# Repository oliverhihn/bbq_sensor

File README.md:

# BBQ Temperature Sensor Project

This project is a BBQ temperature sensor that allows you to monitor the temperature of your BBQ grill or smoker remotely. It uses a Thermocouple with a MAX31855 amplifier temperature sensor to measure the temperature and an ESP8266 (D1 Mini) microcontroller to send the data to a web server. The project is designed to be easy to set up and use.

## PCB Setup

For a more stable and compact design, a custom PCB was created. The PCB is designed to hold the D1 Mini microcontroller and the MAX31855 amplifier.

image:

## ESPHome Setup

The project uses ESPHome to manage the D1 Mini microcontroller. ESPHome is a system that allows you to control your ESP8266/ESP32 devices through simple yet powerful configuration files and control them remotely through Home Assistant.

```yml
esp8266:
  board: d1_mini

spi:
  miso_pin: D0
  clk_pin: D1

sensor:
  - platform: max31855
    name: "BBQ Temperature"
    cs_pin: D2
    update_interval: 10s
```

## Parametric Box

Thank you to [@pbtec_14016](https://www.printables.com/@pbtec_14016) for the original design of the box. The original design was modified to fit the PCB and the D1 Mini microcontroller. The box is designed to be 3D printed and has cutouts for the thermocouple and the D1 Mini microcontroller.

Only things changed from the original design are the Holes in the wall of the box for the cables, the count of screws for the lid, and the dimensions.
The box is designed to be printed in one piece, with no need for supports. The design is parametric, allowing you to easily adjust the dimensions to fit your needs.

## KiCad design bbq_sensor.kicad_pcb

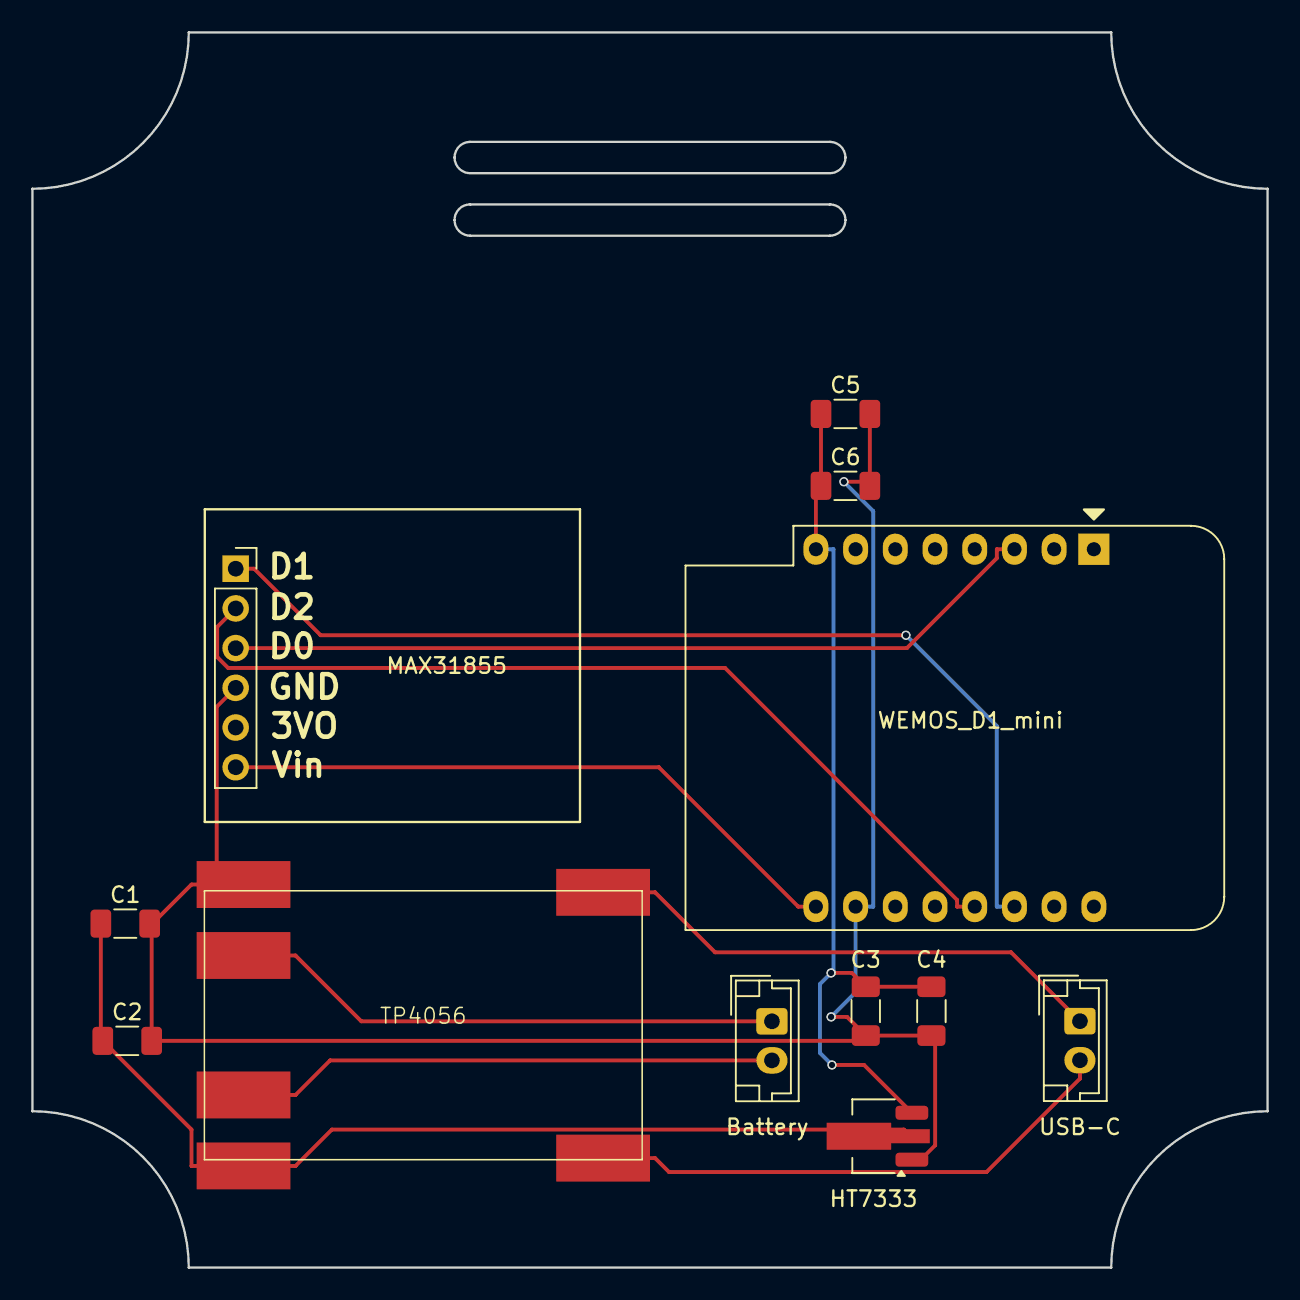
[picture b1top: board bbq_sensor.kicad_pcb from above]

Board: 2 copper layers, 79.0 x 79.0 mm, 12 parts (0 on the bottom side), 11 nets.

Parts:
Battery: Battery_Conn; JST_EH_B2B-EH-A_1x02_P2.50mm_Vertical
C1, C5: 47 µF MLCC; C_1206_3216Metric_Pad1.33x1.80mm_HandSolder
C2: 100 µF Elco; C_1206_3216Metric_Pad1.33x1.80mm_HandSolder
C3: 10 µF MLCC; C_1206_3216Metric_Pad1.33x1.80mm_HandSolder
C4, C6: 0.1 µF MLCC; C_1206_3216Metric_Pad1.33x1.80mm_HandSolder
HT7333: HT7333; SOT-89-3_Handsoldering
MAX31855: Conn_01x06_Socket; PinSocket_1x06_P2.54mm_Vertical
TP4056: tp4056-module
U2: WEMOS_D1_mini; WEMOS_D1_mini_light
USB-C: USB-C_Conn; JST_EH_B2B-EH-A_1x02_P2.50mm_Vertical

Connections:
unnamed: Battery.2 (Battery_+), TP4056.5 (B+)
unnamed: Battery.1 (Battery_-), TP4056.6 (B-)
unnamed: TP4056.1 (Vin+), USB-C.2 (Vin+)
unnamed: TP4056.2 (Vin-), USB-C.1 (Vin-)
unnamed: MAX31855.3 (D0_DO), U2.3 (D0)
unnamed: MAX31855.1 (D1_CLK), U2.14 (SCL/D1)
unnamed: MAX31855.2 (D2_CS), U2.13 (SDA/D2)
unnamed: C1.2, C2.2, C3.2, C4.2, C5.2, C6.2, HT7333.1 (VIN), MAX31855.4 (GND), TP4056.4 (Vout-), U2.10 (GND)
unnamed: MAX31855.6 (VIN), U2.9 (5V)
unnamed: C1.1, C2.1, HT7333.2 (GND), TP4056.3 (Vout+)
unnamed: C3.1, C4.1, C5.1, C6.1, HT7333.3 (VOUT), U2.8 (3V3)

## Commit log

2025-05-19 add readme
2025-05-20 added box
2025-05-20 fix holesize
2025-05-20 added .gitignore
2025-05-21 usb-c port instead of hole
2025-05-21 fix conflict
2025-05-21 decreased box height
2025-05-21 improved pcb
2025-05-21 update image of pcb
2025-05-22 update board
2025-05-23 added caps
2025-05-24 update image
2025-06-08 update box and images
